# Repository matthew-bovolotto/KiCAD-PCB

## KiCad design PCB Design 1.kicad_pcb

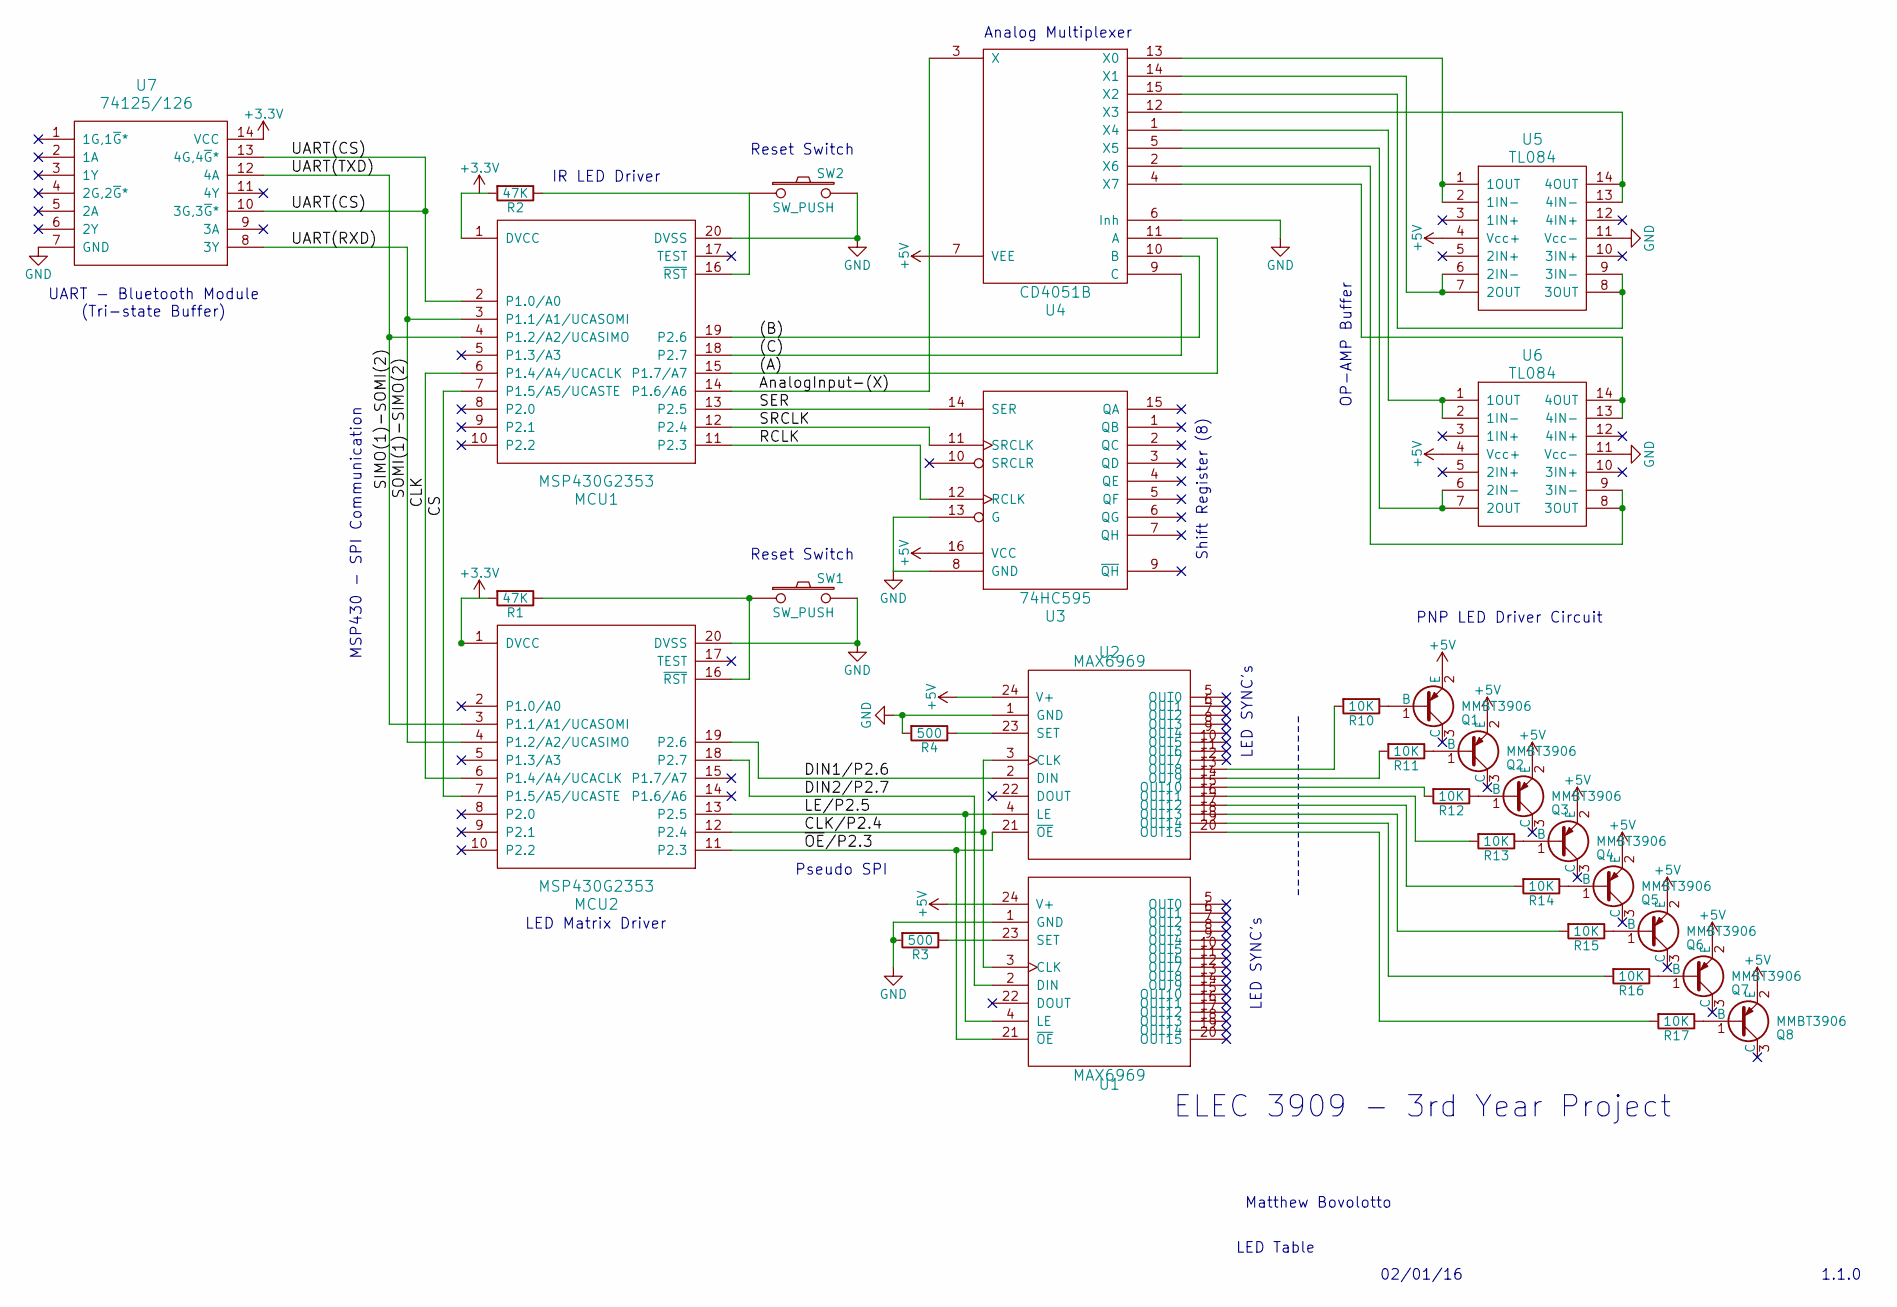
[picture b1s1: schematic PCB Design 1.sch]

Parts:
MCU1, MCU2: MSP430G2353; DIP-20_W7.62mm
Q1, Q2, Q3, Q4, Q5, Q6, Q7, Q8: MMBT3906; TO-92_Inline_Narrow_Oval
R1, R2: 47K; R_0402
R3, R4: 500; R_0402
R10, R11, R12, R13, R14, R15, R16, R17: 10K; R_0402
SW1, SW2: SW_PUSH; SW_SPST_EVPBF
U1, U2: MAX6969; DIP-24_W7.62mm
U3: 74HC595; DIP-16_W7.62mm
U4: CD4051B; DIP-16_W7.62mm
U5, U6: TL084; DIP-14_W7.62mm
U7: 74125/126; DIP-14_W7.62mm

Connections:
/(A): MCU1.15 (P1.7/A7), U4.11 (A)
/(B): MCU1.19 (P2.6), U4.10 (B)
/(C): MCU1.18 (P2.7), U4.9 (C)
/CLK: MCU1.6 (P1.4/A4/UCACLK), MCU2.6 (P1.4/A4/UCACLK)
/CLK/P2.4: MCU2.12 (P2.4), U1.3 (CLK), U2.3 (CLK)
/CS: MCU1.7 (P1.5/A5/UCASTE), MCU2.7 (P1.5/A5/UCASTE)
/DIN1/P2.6: MCU2.19 (P2.6), U2.2 (DIN)
/DIN2/P2.7: MCU2.18 (P2.7), U1.2 (DIN)
/LE/P2.5: MCU2.13 (P2.5), U1.4 (LE), U2.4 (LE)
/RCLK: MCU1.11 (P2.3), U3.12 (RCLK)
/SER: MCU1.13 (P2.5), U3.14 (SER)
/SIMO(1)-SOMI(2): MCU1.4 (P1.2/A2/UCASIMO), MCU2.3 (P1.1/A1/UCASOMI), U7.12 (4A)
/SOMI(1)-SIMO(2): MCU1.3 (P1.1/A1/UCASOMI), MCU2.4 (P1.2/A2/UCASIMO), U7.8 (3Y)
/SRCLK: MCU1.12 (P2.4), U3.11 (SRCLK)
/UART(CS): MCU1.2 (P1.0/A0), U7.10 (3G,3~G~*), U7.13 (4G,4~G~*)
/~OE~/P2.3: MCU2.11 (P2.3), U1.21 (~OE), U2.21 (~OE)
GND: MCU1.20 (DVSS), MCU2.20 (DVSS), R3.2, R4.2, SW1.2, SW2.2, U1.1 (GND), U2.1 (GND), U3.8 (GND), U3.13 (G), U4.6 (Inh), U5.11 (Vcc-), U6.11 (Vcc-), U7.7 (GND)
unnamed: MCU1.16 (~RST), R2.1, SW2.1
unnamed: MCU2.16 (~RST), R1.1, SW1.1
unnamed: Q1.1 (B), R10.1
unnamed: Q2.1 (B), R11.1
unnamed: Q3.1 (B), R12.1
unnamed: Q4.1 (B), R13.1
unnamed: Q5.1 (B), R14.1
unnamed: Q6.1 (B), R15.1
unnamed: Q7.1 (B), R16.1
unnamed: Q8.1 (B), R17.1
unnamed: R3.1, U1.23 (SET)
unnamed: R4.1, U2.23 (SET)
unnamed: R10.2, U2.13 (OUT8)
unnamed: R11.2, U2.14 (OUT9)
unnamed: R12.2, U2.15 (OUT10)
unnamed: R13.2, U2.16 (OUT11)
unnamed: R14.2, U2.17 (OUT12)
unnamed: R15.2, U2.18 (OUT13)
unnamed: R16.2, U2.19 (OUT14)
unnamed: R17.2, U2.20 (OUT15)
unnamed: U4.1 (X4), U6.1 (1OUT), U6.2 (1IN-)
unnamed: U4.2 (X6), U6.8 (3OUT), U6.9 (3IN-)
unnamed: U4.4 (X7), U6.13 (4IN-), U6.14 (4OUT)
unnamed: U4.5 (X5), U6.6 (2IN-), U6.7 (2OUT)
unnamed: U4.12 (X3), U5.13 (4IN-), U5.14 (4OUT)
unnamed: U4.13 (X0), U5.1 (1OUT), U5.2 (1IN-)
unnamed: U4.14 (X1), U5.6 (2IN-), U5.7 (2OUT)
unnamed: U4.15 (X2), U5.8 (3OUT), U5.9 (3IN-)

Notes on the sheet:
LED SYNC's
Reset Switch
PNP LED Driver Circuit
Pseudo SPI
ELEC 3909 - 3rd Year Project
1.1.0
02/01/16
LED Table
Matthew Bovolotto
Analog Multiplexer
Shift Register (8)
UART - Bluetooth Module (Tri-state Buffer)
MSP430 - SPI Communication
IR LED Driver
LED Matrix Driver
OP-AMP Buffer

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
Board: 2 copper layers, 31 parts (0 on the bottom side), 49 nets, no tracks yet.

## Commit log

2016-01-27 Second Commit - TL084's left to implement
2016-02-01 UART Tri-State Buffer Update
2016-02-01 Schematic images
2016-02-01 OP AMP Buffer Added
2016-02-05 Minor Pin Updates
2016-03-03 IR Led Driver Update
2016-03-07 IR LED fix
